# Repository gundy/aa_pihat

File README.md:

# AA Boards and Tools

This repository contains some schematics and board designs that have been useful when trying to understand the communications used by the AA system.

- [An interceptor board](./hardware/boards/aa_interceptor/README.md) that sits between the tablet and CB and allows the RS485 lines to be read.
- [A 'hat' for a Raspberry Pi](./hardware/boards/pi_hat/README.md) that uses the 14v supply to power the Pi, and provides circuitry to allow the PI's built-in serial port to communicate with the RS485 data bus.

As always, YMMV. Verify designs before using them. Don't mess with stuff you can't afford to break.

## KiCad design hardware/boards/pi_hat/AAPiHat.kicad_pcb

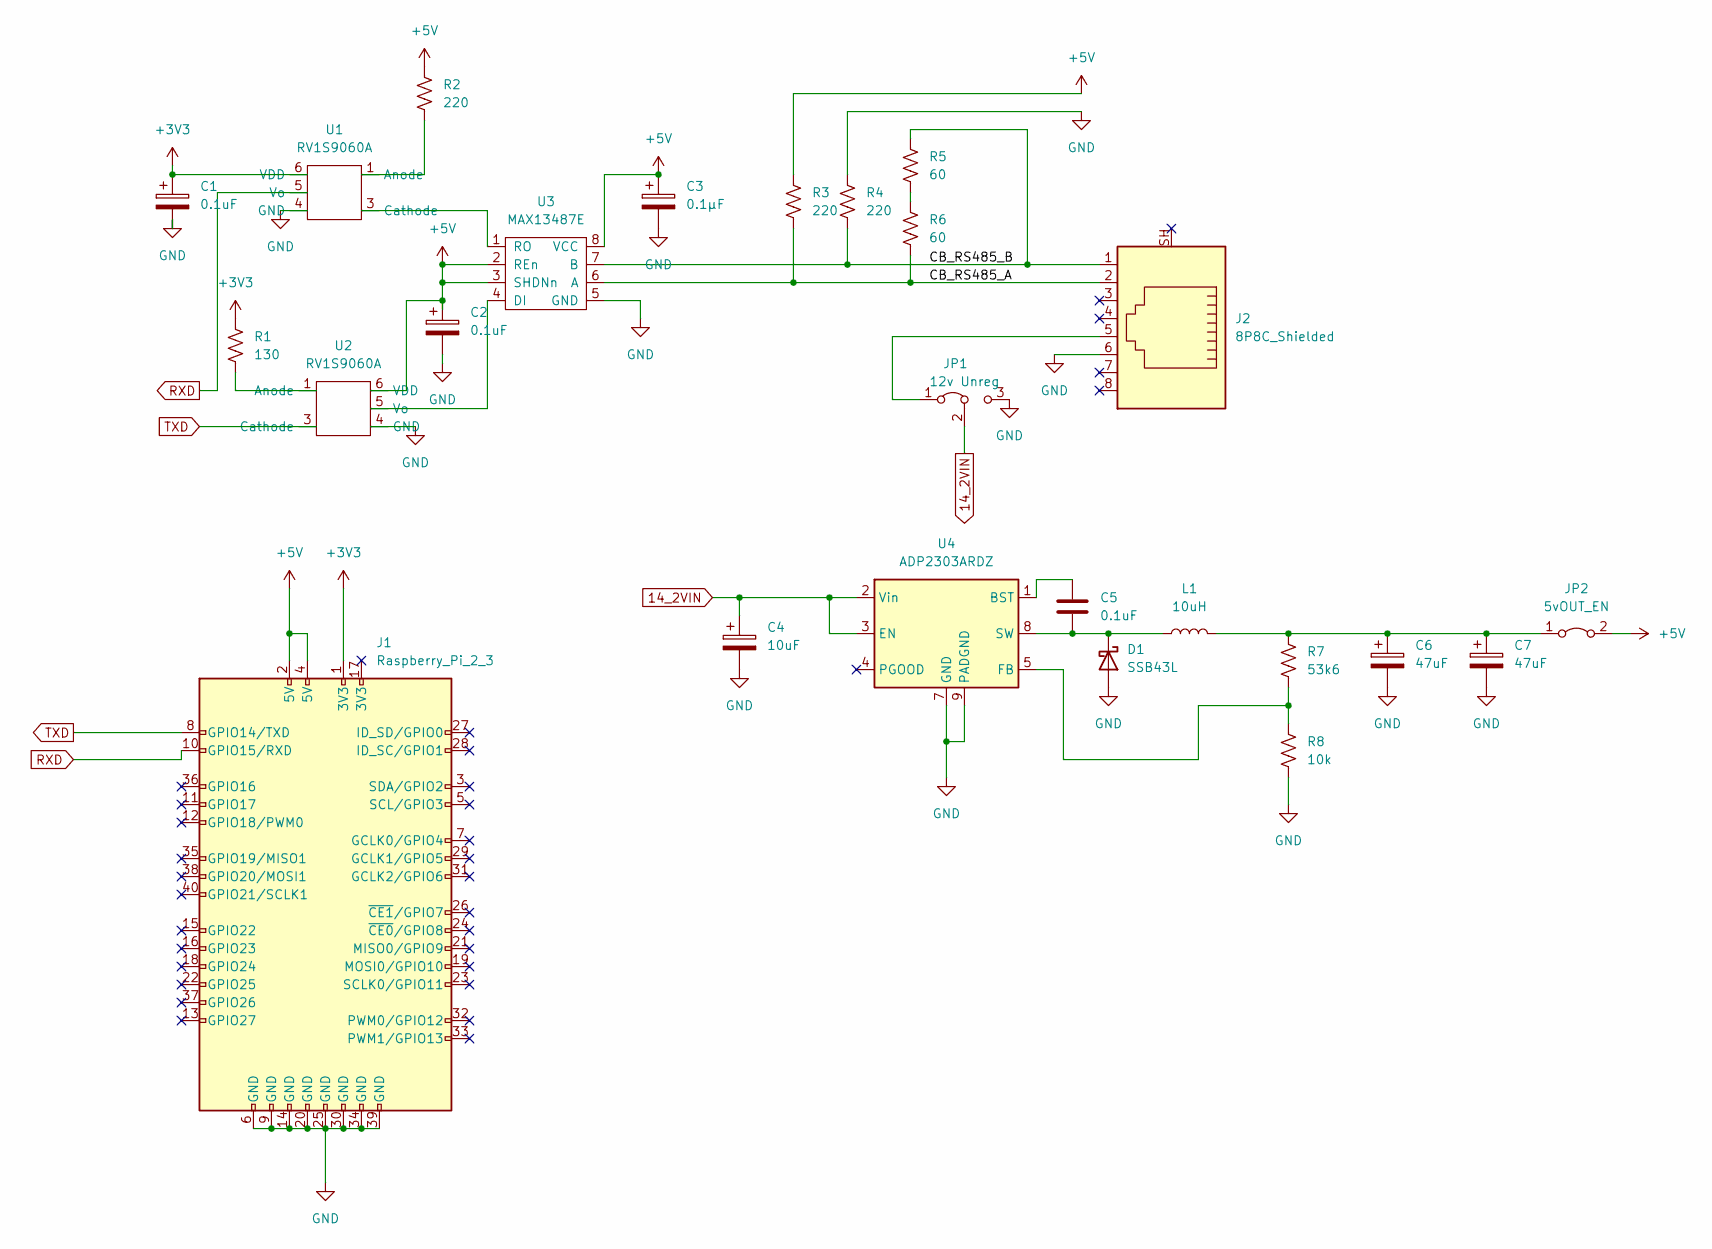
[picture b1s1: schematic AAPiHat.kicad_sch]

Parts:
C1, C2, C5: 0.1uF; C_1210_3225Metric_Pad1.33x2.70mm_HandSolder
C3: 0.1µF; C_1210_3225Metric_Pad1.33x2.70mm_HandSolder
C4: 10uF; C_1210_3225Metric_Pad1.33x2.70mm_HandSolder
C6, C7: 47uF; C_1210_3225Metric_Pad1.33x2.70mm_HandSolder
D1: SSB43L; D_SMB_Handsoldering
J1: Raspberry_Pi_2_3; PinHeader_2x20_P2.54mm_Vertical
J2: 8P8C_Shielded; RJ45_Wuerth_615008142621_Horizontal
JP1: 12v Unreg; PinHeader_1x03_P2.54mm_Vertical
JP2: 5vOUT_EN; PinHeader_2x01_P2.54mm_Vertical
L1: 10uH; L_12x12mm_H8mm
R1: 130; R_1210_3225Metric_Pad1.30x2.65mm_HandSolder
R2, R3, R4: 220; R_1210_3225Metric_Pad1.30x2.65mm_HandSolder
R5, R6: 60; R_1210_3225Metric_Pad1.30x2.65mm_HandSolder
R7: 53k6; R_1210_3225Metric_Pad1.30x2.65mm_HandSolder
R8: 10k; R_1210_3225Metric_Pad1.30x2.65mm_HandSolder
U1, U2: RV1S9060A; SO-5_4.4x3.6mm_P1.27mm
U3: MAX13487E; SO-8_3.9x4.9mm_P1.27mm
U4: ADP2303ARDZ; SOIC-8-1EP_3.9x4.9mm_P1.27mm_EP2.29x3mm

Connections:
14_2VIN: C4.1, JP1.2 (C), U4.2 (Vin), U4.3 (EN)
+3V3: C1.1, J1.1 (3V3), R1.1, U1.6 (VDD)
+5V: C2.1, C3.1, J1.2 (5V), J1.4 (5V), JP2.2 (B), R2.1, R3.2, U2.6 (VDD), U3.2 (REn), U3.3 (SHDNn), U3.8 (VCC)
/CB_RS485_A: J2.2, R3.1, R6.2, U3.6 (A)
/CB_RS485_B: J2.1, R4.2, R5.1, U3.7 (B)
GND: C1.2, C2.2, C3.2, C4.2, C6.2, C7.2, D1.2 (A), J1.6 (GND), J1.9 (GND), J1.14 (GND), J1.20 (GND), J1.25 (GND), J1.30 (GND), J1.34 (GND), J1.39 (GND), J2.6, JP1.3 (B), R4.1, R8.2, U1.4 (GND), U2.4 (GND), U3.5 (GND), U4.7 (GND), U4.9 (PADGND)
unnamed: C5.1, D1.1 (K), L1.1, U4.8 (SW)
unnamed: C5.2, U4.1 (BST)
unnamed: C6.1, C7.1, JP2.1 (A), L1.2, R7.1
unnamed: J2.5, JP1.1 (A)
unnamed: R1.2, U2.1 (Anode)
unnamed: R2.2, U1.1 (Anode)
unnamed: R5.2, R6.1
unnamed: R7.2, R8.1, U4.5 (FB)
unnamed: U1.3 (Cathode), U3.1 (RO)
unnamed: U2.5 (Vo), U3.4 (DI)
RXD: J1.10 (GPIO15/RXD), U1.5 (Vo)
TXD: J1.8 (GPIO14/TXD), U2.3 (Cathode)

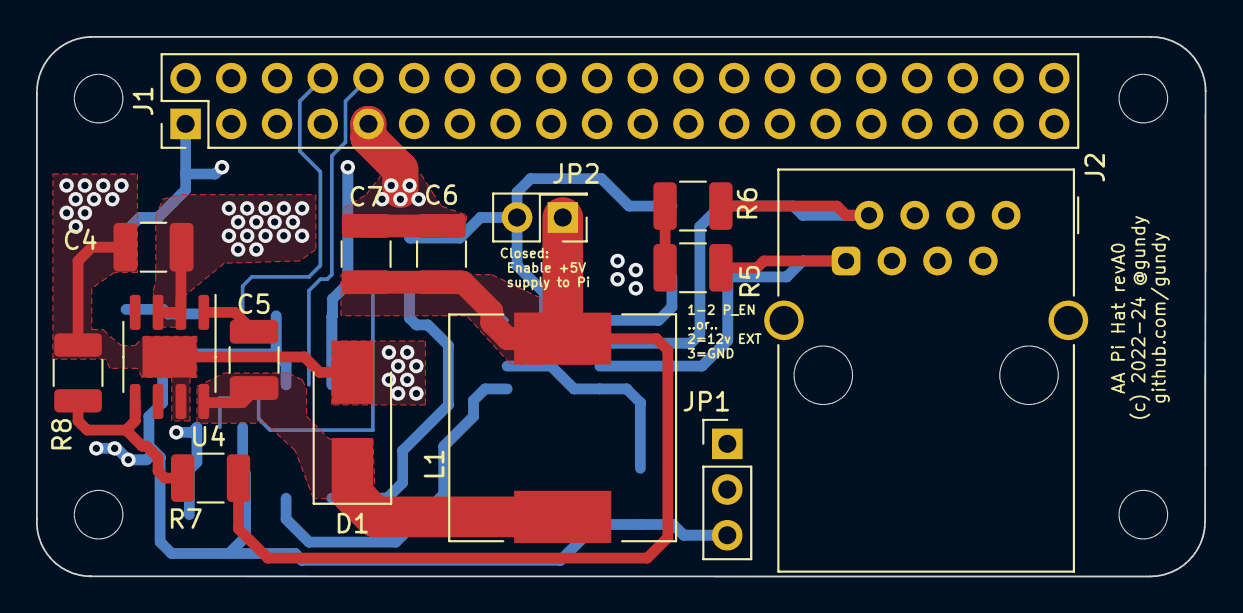
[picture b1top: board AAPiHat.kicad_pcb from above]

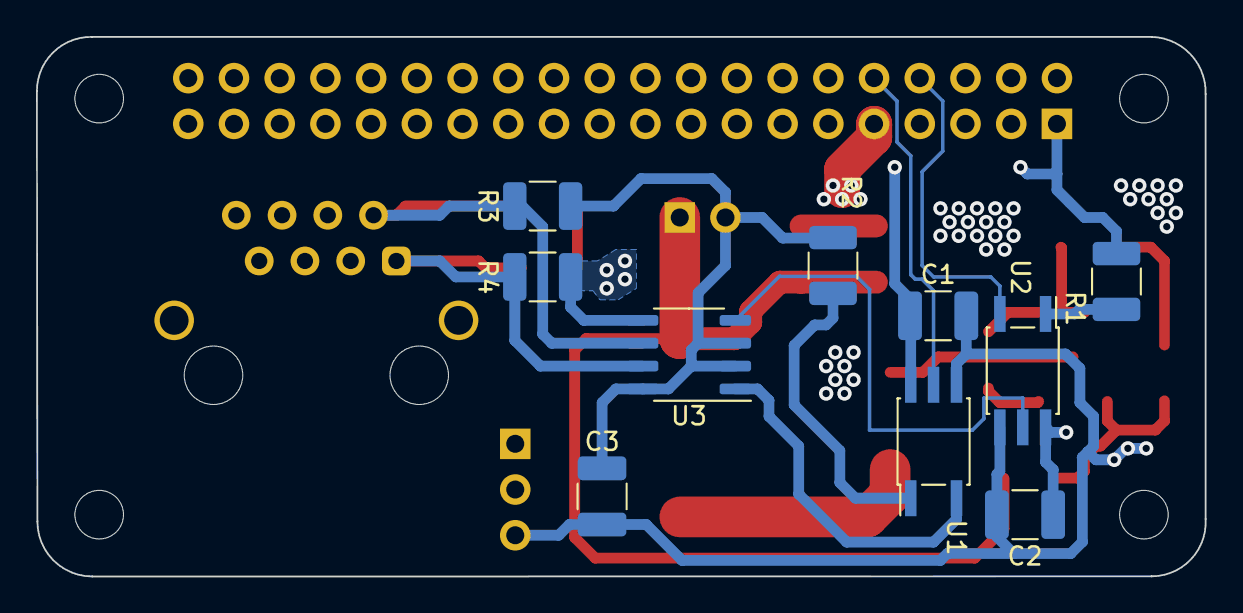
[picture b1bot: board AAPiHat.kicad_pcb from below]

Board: 4 copper layers, 64.9 x 30.0 mm, 25 parts (10 on the bottom side), 18 nets.

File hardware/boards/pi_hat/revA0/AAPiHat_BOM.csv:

"Id";"Designator";"Package";"Quantity";"Designation";"Supplier and ref";
1;"JP1";"PinHeader_1x03_P2.54mm_Vertical";1;"12v";;;
2;"D1";"D_SMB_Handsoldering";1;"SSB43L";;;
3;"C5,C2,C1";"C_1210_3225Metric_Pad1.33x2.70mm_HandSolder";3;"0.1uF";;;
4;"C4";"C_1210_3225Metric_Pad1.33x2.70mm_HandSolder";1;"10uF";;;
5;"C7,C6";"C_1210_3225Metric_Pad1.33x2.70mm_HandSolder";2;"47uF";;;
6;"R6,R5";"R_1210_3225Metric_Pad1.30x2.65mm_HandSolder";2;"60";;;
7;"L1";"L_12x12mm_H8mm";1;"10uH";;;
8;"JP2";"PinHeader_2x01_P2.54mm_Vertical";1;"5vOUT_EN";;;
9;"R7";"R_1210_3225Metric_Pad1.30x2.65mm_HandSolder";1;"53k6";;;
10;"R8";"R_1210_3225Metric_Pad1.30x2.65mm_HandSolder";1;"10k";;;
11;"J2";"RJ45_Wuerth_615008142621_Horizontal";1;"Wurth RJ45";;;
12;"U4";"SOIC-8-1EP_3.9x4.9mm_P1.27mm_EP2.29x3mm";1;"ADP2303ARDZ";;;
13;"J1";"PinHeader_2x20_P2.54mm_Vertical";1;"Raspberry_Pi_2_3";;;
14;"R2,R3,R4";"R_1210_3225Metric_Pad1.30x2.65mm_HandSolder";3;"220";;;
15;"U1,U2";"SO-5_4.4x3.6mm_P1.27mm";2;"RV1S9060A";;;
16;"R1";"R_1210_3225Metric_Pad1.30x2.65mm_HandSolder";1;"130";;;
17;"U3";"SO-8_3.9x4.9mm_P1.27mm";1;"MAX13487E";;;
18;"C3";"C_1210_3225Metric_Pad1.33x2.70mm_HandSolder";1;"0.1µF";;;

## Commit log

2024-08-31 LICENSE -> LICENSE.md
2024-08-31 Add rendered board image to readme
2024-08-31 Add schematics and board layout for RS485 interceptor module.

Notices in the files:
hardware/boards/pi_hat/AAPiHat.kicad_pcb:
(c) 2022-24 @gundy
